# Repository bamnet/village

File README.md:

# Village Electric Light Department

_(village, for short)_

## Background

I have a collection of 1-2 dozen Department 56 lighted Christmas houses. The default
lighting solution has a big problem though: a house is either lit or not. Further,
the default technique of daisy-chaining all of the plugs together means the entire
village is typically on or off.

This is not very realistic, our winter Dickens Village is not North Korea.

## Goal

The Village Electric Light Department provides the ability for each house to be
individually dimmed and to have that brightness vary throughout the night. This
enables much more custom and realistic displays, with each house following its
own lighting pattern throughout the night and across different nights.

## Approach

### 2018?

In 2018 we built our first prototype. To do this, we bought an RGB LED strip and cut
it into individual segments. We soldered wires onto each segment, and wired them all
back into a TLC5947 controlled by an ESP32.

Each house got one cut segment of a 12 V analog (not individually addressable) RGBW
strip (Shiji Lighting SJ-10060-RGBW, 60 LEDs/m). A segment has 3 warm-white 5050 RGBW
LEDs. Each color channel runs its 3 LEDs in series with a current-limiting resistor
(150 ohm on G/B/W), roughly 20 mA per channel. The TLC5947 sank each channel's
current. See `archive/2018_led_segment.jpg`.

This was a good proof of concept, but the construction was quite messy with flexible
LED strip segments haphazardly positioned in the back / bottom lighting holes of the
houses, a messy breadboard wiring this all together, and standalone power supply.

### 2020?

We started cleaning up this design by introducing a circular PCB with LEDs that we
could fit into a 3D printer holder for each house. These could, in theory, be wired
back to a base station for control.

Ultimately, we never finished a working end-to-end design here, largely driven by
the manual work to solder connectors onto each of the PCBs and, more importantly,
the manual work to build custom cables to connect the PCBs back to the base station.

### 2025

We specified a two-board design (ESP32-S3 base station running WLED, plus a
daisy-chained 20 mm Pixel PCB with SK6812 RGBW LEDs) and started a controller
layout. Nothing was fabricated because we ran out of time.

## Specifications

Requirement keywords (MUST, SHOULD, MAY) follow RFC 2119. Items marked **TBD** are
open decisions.

### System

- The system MUST support 22 houses.
- Each house MUST be independently addressable, so its brightness can be set on
  its own. Addressing each LED within a house MAY be supported, but is not required.
- Houses SHOULD be daisy-chained, with the base station driving about 4 chains
  (roughly 6 houses per chain). This keeps cables short and the base station tidy.
  It is a preference, not a hard requirement: another topology is acceptable if
  it is clearly better.

### Physical layout

- Tentatively, the base station sits in the middle, between two shelves, with chains
  running outward on both sides.
- Houses are spaced about 1 ft (0.3 m) apart. A house-to-house cable of about 1 m
  gives enough slack.
- The farthest house is no more than 8 ft (2.4 m) from the base station.

### Light

As a winter village, each house MUST be lit using warm white light. Each house MAY
support RGB to fine tune the colors and do neat patterns.

The light should be bright, historically using a 5 - 6 watt C7 bulb @ 120 volts.
We obviously want to modernize this with an LED.

- Research (2026-09) shows small incandescent C7 bulbs are dim. Retail listings give
  a 4 W clear C7 as 16 - 19 lm, and a 5 W, 130 V-rated C7 as about 10 lm. LED
  "5 W equivalent" C7 bulbs claim 50 - 75 lm, but those figures are marketing, not
  measurements. The 2025 spec's "~60 lm" target is probably 3x too high.
- The 2018 prototype segment was bright enough, even with its poor LED placement on
  a flexible strip. It had 3 warm-white RGBW 5050 LEDs per house, each channel's LEDs
  in series at about 20 mA.
- Brightness target: warm-white output per house SHOULD match the 2018 segment,
  meaning 3 warm-white RGBW 5050 LEDs driven at about 16 - 20 mA.
- Each house MUST use one WS2814 as its driver. It is a 4-channel RGBW
  constant-current driver that WLED supports (configured as SK6812 RGBW type). Its
  outputs are fixed at 16.5 mA per channel, about 80% of the 2018 current.
  **TBD:** confirm this is bright enough.
- As of 2026-09-30, the original SOP-12 WS2814 (C965562) shows 0 stock at LCSC.
  The draft schematic uses the WS2814F (FSOP-8, C5446694, about 107,000 in stock).
  It has the same 16.5 mA outputs, the same 9 V DIN rating, and the same 12 V
  application circuit (2.7k to VDD, 0.1 uF). It has no backup data input (DIN2),
  so there is nothing to tie off. Its data order is W, R, G, B (datasheet p. 4).
  The WS2814A (SOP-8, C2920044, about 7,800 in stock) is the same die in a larger
  package. It is the fallback, with a standard SOIC-8 footprint.
- Decided (2026-09-30): the Pixel PCB uses the WS2814F. Its smaller body leaves
  more room for the LEDs on the 20 mm board.
- The WS2814F's FSOP-8 footprint (1.65 x 3.25 mm body, 2.85 mm lead span, 0.8 mm
  pitch) is not in KiCad's stock libraries, so we drew it. Once it's proven on a fabricated
  board, consider contributing it (and a WS2814 symbol) upstream to the KiCad
  libraries.
- Each channel drives 3 LEDs in series, and all 3 LEDs show the same color, with one
  address per house. The white channel MUST be warm white (2700 - 3000 K).
- LEDs SHOULD be 3 RGBW 5050 4-in-1 packages with a warm-white die, matching 2018.
  Fallback: 3 RGB LEDs plus 3 separate warm-white LEDs, which also allows a free
  choice of warm-white LED.
- As of 2026-09, LCSC has two warm-white 4-in-1 RGBW 5050 parts (SMD5050-8P, with
  a separate anode and cathode pin per color). Both are JLCPCB extended parts.
  Figures are from the datasheets, at 20 mA:
  - Honglitronic HL-5050RGBW-S1-A27 (C22470444): about 11,000 in JLCPCB stock.
    The "-A27" suffix is the datasheet's white bin A27, which is 2580 - 2870 K.
    That is slightly warmer than 2700 - 3000 K at the low end. White gives 7 - 9 lm,
    CRI 80 or better. Forward voltage is 2.8 - 3.4 V (W/G/B) and 1.8 - 2.4 V (R).
  - TCWIN TC5050RGBW3D06-4CSAR3-AFW324A (C784543): 2800 - 3200 K. White gives
    6 - 7 lm, CRI 80 - 85, with a forward voltage of 2.8 - 3.2 V. Stock is low
    (about 240 at JLCPCB, 860 at LCSC).
  - Cool-white variants that do not meet the spec: XINGLIGHT XL-5050RGBW
    (C7371891), TCWIN C784545 (6000 - 6500 K), and C784544 (3800 - 4200 K).
  **Chosen: Honglitronic C22470444.** We tested samples of both parts in 2026-11.
  The Honglitronic white was warmer and slightly preferred. Its spec sheet
  (B-18-A-1651 rev A/2, 2019) has "Under Development" checked on its cover, not
  "Mass production", but JLCPCB stocks it, so this looks like stale paperwork.
- Heat is not expected to be a concern. The cut-up LED strip prototype ran without
  heat problems.
- Driver heat (estimated): 3 red LEDs drop only 5.4 - 7.2 V, which leaves up to
  about 6.6 V across the WS2814's red output (about 110 mW at 16.5 mA). The draft
  adds a 120 ohm ballast resistor (R4) on red to take about 2 V (33 mW) of that off
  the chip. With all four channels at full, the WS2814 then dissipates about
  0.2 W worst case. Warm-white-only use is well below this.
- The two LED candidates number their pins differently. Honglitronic has anodes on
  pins 1/3/5/7 (W/B/G/R) and cathodes on 2/4/6/8. TCWIN has anodes on 1-4 (R/G/B/W)
  and cathodes on 8-5. Physically they match: with the corner mark at the top
  left, looking at the lens, both put the anodes on the right with white at the
  top, and each cathode is directly across from its anode. A multimeter check of
  both samples (2026-11) confirmed this for white. The schematic and footprint use
  the Honglitronic numbering.

### Interconnect

The lack of a practical cable solution is what stalled the 2020 attempt, so it is a
first-class requirement here.

- Cables MUST be off-the-shelf or easily purchasable. We MUST NOT need to crimp,
  solder, or otherwise build our own cables (the system needs about 24 of them).
- House-to-house links need cables of about 1 m. **TBD:** the length from the base
  station to the first house in each chain.
- The WS2814 datasheet specifies data runs of up to 2 m between two points without
  extra circuitry. The base-station-to-first-house run SHOULD stay within about 2 m.
  Otherwise the base station needs a stronger line driver.
- Cables MUST be standard 3-wire RC servo extension cables (JR/Futaba style, 2.54 mm
  pitch), bought ready-made. 1 m male-to-female cables are widely sold. 22 AWG is
  preferred over 26 AWG for lower voltage drop.
- Boards MUST use 2.54 mm pitch 1x3 headers: male pins for the incoming cable and a
  female socket for the outgoing cable. JLCPCB SHOULD solder these through-hole
  parts (v0.1 headers were hand-soldered; see the Pixel PCB section).
- Pinout MUST put power on the middle pin, following the servo convention. Then a
  reversed plug swaps ground and data rather than shorting the supply. The design
  SHOULD tolerate a reversed plug without damage, using series resistors on data
  lines and similar measures. This is to be verified during design: in a reversal,
  a house's ground rides on the upstream data line, and the WS2814 data input is
  rated to only 9 V.
- Draft protection (Pixel PCB schematic v0.1, estimated rather than tested):
  - Reversed plug: this house's GND pin lands on the upstream data line. The
    return current of this house and every house downstream is about 2.6 mA per
    house through its 2.7k VDD resistor, so about 16 mA for 6 houses, since the
    LEDs stay dark with no valid data. Most of it flows through the upstream
    house's R3 (100 ohm) into the upstream WS2814's DOUT. For the first house in
    a chain, it flows into the Dig-Quad's output buffer instead. Only about
    1 - 2 mA goes through this house's R2 (1k) and D1. The part at risk is
    therefore the upstream driver. The datasheet rates DOUT sink current at 10 mA
    minimum at 0.4 V (p. 3), which is less than 16 mA. While the upstream DOUT is
    high, this house's ground rises to about 5 V. The current then splits between
    R2/D1 (about 5 mA) and the upstream chip's VDD. D1's job is to clamp DIN so it
    can't go below this house's lifted GND.
  - Offset plug (a socket shifted one pin over on the header): 12 V can land on the
    data pin. R2 limits this to about 7 mA into VDD through D1, so R2 dissipates
    about 45 mW (the 0402 is rated 62.5 mW). The pass/fail limit is the datasheet's
    VDD absolute maximum of 3.7 - 5.3 V (p. 2), so VDD must stay at or below 5.3 V.
  - Why keep D1: the datasheet limits logic input voltage to "VDD-0.7 ~ VDD+0.7"
    (p. 2). The lower bound is almost certainly a typo for -0.7 V. Either way, DIN
    may go only about 0.7 V beyond the rails. The BAT54S (Vf about 0.3 V) keeps
    DIN inside that window in both the reversed and offset cases. A series
    resistor alone would not.
  - DOUT keeps the datasheet's 100 ohm series resistor.
  - **TBD:** the R2 value. Test on the first fabricated Pixel boards (the LED
    samples on order don't include a WS2814F):
    - Reversed plug: check that the upstream DOUT and the Dig-Quad output survive
      and still work afterward.
    - Offset plug: measure VDD with 12 V on DATA_IN. It must stay at or below 5.3 V.
    No circuit change is planned until those results are in.
- Flat servo cable fits the original cord channel. It is thinner than the classic
  120 V lamp cord that already uses it.

### Power

- The system MUST use a 12 V supply. We chose 12 V over 5 V because of voltage drop.
  5 V SK6812 LEDs need at least 4.5 V at the last house, which leaves only about
  0.5 V for losses across a chain of servo cables. At 12 V, 3 white/blue/green LEDs
  in series need about 9 - 9.6 V (3.0 - 3.2 V each). Allowing for the driver output,
  that leaves roughly 1.5 V of headroom. These are estimates: the WS2814 datasheet
  does not specify the minimum output voltage it needs to regulate.
- Estimated load: about 66 mA per house with all four channels at full, so about 1.5 A
  (18 W) for 22 houses. With warm white only, it is about 16.5 mA per house, so about
  0.4 A.
- Estimated voltage drop: about 0.6 V at full RGBW for a 6-house chain on 26 AWG
  cable (about 2 m to the first house, then 1 m hops). This is within the headroom.
- For the prototype, power enters through the Dig-Quad's input screw terminals.
  **TBD:** a supply sized with margin (for example 12 V, 3 A or more).

### Pixel PCB

- The project targets KiCad 10. Files saved in KiCad 10 cannot be opened in
  KiCad 9.
- Draft schematic: `hardware/pixel/pixel.kicad_sch` (v0.1). It was authored in
  KiCad 9 format and is ERC clean in KiCad 9.0.2 and 10.0.6.
- Custom footprints live in the project library `hardware/pixel/village.pretty`
  (nickname `village`), since neither part is in KiCad's stock libraries:
  - `FSOP-8_1.65x3.25mm_P0.8mm` (U1, WS2814F). From the datasheet package drawing
    (V1.1, p. 6): 0.35 mm leads with 0.4 mm feet. The land pattern is 0.9 x 0.45 mm
    pads centered 2.6 mm apart (0.3 mm toe, 0.2 mm heel).
  - `LED_Honglitronic_HL-5050RGBW_5.0x5.0mm_P1.2mm` (D2-D4). This is the
    manufacturer's recommended land pattern (spec B-18-A-1651 rev A/2, p. 3):
    1.1 x 0.54 mm pads, 2.83 mm inner gap, 1.2 mm pitch. Pads are numbered as in the
    datasheet's top view: anodes 1/3/5/7 on the right, cathodes 2/4/6/8 on the
    left, pin 1 at the top right. The part's corner mark sits at pin 2 (white
    cathode), and the footprint's silkscreen tick and Fab chamfer mark that
    corner. KiCad's usual pin-1 marking would put the tick on the white anode,
    which would make a correctly placed LED look rotated in review.
  - The LED datasheet's "bottom view" labels the pins the same as its top view,
    not mirrored, so one of the two views is wrong. A 2026-11 multimeter check of
    a sample (diode mode, red lead on the anode) showed that the top view is
    correct. With the corner mark at the white cathode, the white anode is directly
    across from it. That is the footprint as drawn, not a mirror image.
  - **TBD:** both footprints are unproven until a fabricated board is assembled and
    works. The TCWIN LED would fit the same pads, but its symbol pin numbers would
    need remapping, because its pad numbering differs.
- In order to fit the 3D-printed holder that sits in each house's lighting hole,
  the per-house PCB ("Pixel PCB") MUST be a circle no bigger than 20 mm in diameter.
  This is small, but large enough to fit several LEDs as needed.
- The lighting hole in the house itself is slightly larger than the holder hole. The
  hole size is broadly consistent across houses (the original lights are
  interchangeable). **TBD:** the measured house hole size.
- Some houses have the lighting hole in the back and some in the bottom. For bottom
  holes, the original clip-in lamp sits in the hole and its cord leaves sideways,
  flush with the base, through a notch and cord channel in the house base.
- For bottom holes, the assembly can extend up to about 1 in (25 mm) into the house.
- A daisy-chained house has two cables (in and out). Both MUST fit through the notch
  and cord channel. Two flat servo cables fit, since a classic 120 V lamp cord does.
- LEDs MUST be on the top side, clustered near the center. Headers (through-hole)
  go on the bottom side.
- All surface-mount parts, the WS2814 included, SHOULD also go on the top side. That
  keeps assembly to one surface-mount side, which is simpler and cheaper. Moving the
  WS2814 to the bottom is allowed if the LEDs don't fit otherwise, but it requires
  JLCPCB two-sided (Standard) assembly. Settled in layout: every surface-mount
  part, the WS2814F included, is on the top side.
- Through-hole header pins and solder joints come out on the LED side. Headers
  MUST sit near the rim, with a centered keep-out for the LEDs.
- Headers SHOULD be right-angle, mounted side by side on the bottom, with both
  pointing the same way (toward the cord notch). The plugs then lie flat under the
  board. This gives a much lower profile than vertical headers, and both cables
  already point where they need to go. JLCPCB-assemblable candidates: male C492411
  and female C2897385. If two plugs don't fit side by side on the 20 mm board, fall
  back to vertical headers. **TBD:** confirm the fit with real servo plugs (the
  width is estimated at about 8 mm each).
- Provisional layout (placed and routed, pending real plug dimensions):
  `hardware/pixel/pixel.kicad_pcb`.
  - The board is a 20 mm circle. The cord notch is taken to be at the south
    (+Y) edge.
  - J1 and J2 are on the bottom side, with pin rows side by side about 4 mm north
    of center. Their bodies point south and run under the board, so the plugs
    mate near the south rim and lie flat. This works because the headers and
    plugs are on the bottom while every other part is on the top, so the header
    bodies can sit under the top-side parts.
  - This relaxes "headers near the rim". The pin rows sit just north of the
    LEDs, and the LED cluster sits about 2.5 mm south of center.
  - The header rows are 8.9 mm apart, center to center. KiCad's stock
    footprints need at least 8.62 mm, which is slightly more than the estimated
    8 mm plug width.
  - J1 and J2 use KiCad's stock right-angle footprints. Checked against the LCSC
    drawings on 2026-09-30, and the copper matches:
    - J1, male (XFCN PZ254R-11-03P, C492411): Ø1.02 mm holes and 0.64 mm square
      pins (0.91 mm across the corners, so they fit the 1.0 mm drill). The
      body's front face is 4.4 mm from the pin row, and the pin tips are at
      10.4 mm (KiCad draws 4.04 mm and 10.04 mm).
    - J2, female (HCTL PM254-1-03-W-8.5, C2897385): Ø1.02 mm holes. The 8.5 mm
      body ends 10.2 mm from the pin row (KiCad draws 10.03 mm), and the body is
      8.02 mm wide (KiCad draws 7.62 mm). A purchased sample measured about
      8.09 mm wide (2026-11).
    - KiCad's courtyards still cover both real bodies. With the rows 8.9 mm apart,
      the bodies are about 1.1 mm apart.
    - The pin tails are 3.0 and 3.2 mm long, so on a 1.6 mm board they stick up
      about 1.4 - 1.6 mm on the LED side.
  - Pin order: the stock footprints put J1's pin 1 at the west end and J2's pin 1
    at the east end, so the two GND pins are adjacent. Neither part is polarized,
    so this only decides which way up each cable plugs in.
  - Silkscreen markings for plugging in and for JLCPCB's assembly review:
    - Bottom: a filled triangle points at each header's pin 1 (data), with "+" and
      "-" at the other pins. These shapes read the same whether or not they are
      mirrored.
    - Bottom: "JLCJLCJLCJLC" marks where JLCPCB should print its order number.
      The 2026-11 order form had no "Specify a location" option, so v0.1 was
      ordered with "Mark on PCB: Remove Mark" instead.
    - Top: "v0.1", and a pin-1 dot inside U1's outline. The footprint's pin-1
      silkscreen line is clipped by J1's GND pad, so without the dot the top and
      bottom lines would look alike.
    - The LEDs keep their pin-1 tick. D1 uses KiCad's stock SOT-23 outline.
  - On the top side, the LEDs follow the chain +12V -> D2 (east, rot 90) -> D3
    (south, rot 0) -> D4 (west, rot 270) -> U1. Each LED faces the side that
    connects to the next LED toward it, so each group of four color nets between
    LEDs fans diagonally with no crossings. D4's R/G/B cathodes sit just below
    U1's matching outputs. U1 is between D4 and D2, with R4 on the red output and
    C1 beside the VDD pin. D1, R1, C2 and R2 sit above the header pin rows.
  - Routed with Freerouting 2.4.1: 4 vias. +12V and GND are 0.4 mm (a Power
    netclass), because up to ~0.4 A passes through to the rest of the chain.
    Signals are 0.2 mm. VDD narrows to 0.15 mm around U1, and the board minimum
    is set to 0.15 mm to allow it.
  - DRC: 0 errors, 0 unconnected. JLCPCB's limits are enforced by
    `pixel.kicad_dru` and the board setup.
  - Routing workflow: export the DSN with KiCad's Python module
    (`pcbnew.ExportSpecctraDSN`). Route with Freerouting's bundled launcher,
    because the standalone jar needs Java 25. Import the session in KiCad with
    File -> Import -> Specctra Session. Konnect's own DSN export refuses this
    board (round outline, back-side headers, custom rules).
  - JLCPCB export: Konnect's `export_manufacturing_package` with the board open in
    KiCad, `fab_house` jlcpcb, all copper/paste/silkscreen/mask layers plus
    Edge.Cuts, BOM fields `Value,Reference,Footprint,LCSC`, and
    `jlcpcb_cpl_corrections_path` set to `jlcpcb_cpl_corrections.json`. That file
    rotates U1 by 270 degrees and D1 by 180 degrees in the CPL. Both values came
    from comparing our footprints with JLCPCB's EasyEDA footprints for the BOM parts.
    The same comparison reproduces Konnect's preview-verified SOIC-8 rule. The LEDs
    need no correction. JLCPCB's placement preview for v0.1 confirmed U1, D1 and
    the LEDs.
  - JLCPCB's Economic assembly is single-sided, so it leaves off the bottom-side
    headers J1 and J2. Standard assembly can do both sides but needs a board of at
    least 70 mm. v0.1 (5 boards) was assembled top side only, with J1/J2
    hand-soldered.
  - **TBD:** for the 22-board run, either order a JLCPCB panel of at least 70 mm
    (for example 4 x 4) with Standard two-sided assembly, or move the headers so
    that single-sided assembly covers them. Hand soldering MUST be kept to a
    minimum.
  - Manufacturing releases live in `hardware/pixel/production/<version>/`, named
    after the silkscreen version. Each has the exact uploaded files and a
    `MANIFEST.md` with the source commit, file hashes, checks, and the order
    record. When an order is placed, fill in the manifest and tag the commit
    `pixel-<version>`. An ordered release is never changed. A design change bumps
    the silkscreen version and gets a new folder.
  - **TBD:** revisit the header positions once real plugs are measured. The
    house holder now favors vertical headers; see "Feedback for Pixel PCB v0.2"
    in the House holder section.
- The connector, the holder, or both SHOULD let the cables make the turn into the
  channel without stressing the connectors or their solder joints.

### House holder

A 3D-printed holder fits each Pixel PCB into a house's lighting hole. The houses are
Department 56. Their stock cord holds the bulb with bent spring-steel clips that
grip the hole's edge.

Draft OpenSCAD: `hardware/holder/` (OpenSCAD 2021.01). Z = 0 is the wall's outer face,
and +Z points into the house.

#### Measurements

- 2026 notes (7 houses): hole Ø25 - 28 mm, wall 3 - 6 mm. Three bottom-lit houses
  also have an "inlet" of 12 - 13 mm, which is the depth of the recess around the
  hole.
- 2021 spreadsheet (12 houses): wall 4 - 8 mm (8 is the Bakery).
- The same houses differ between the two years by up to 2 mm (Fezziwig 4 vs 6,
  Curiosity 5 vs 4). Treat this as measurement noise.
- The 2021 printed plugs (gcode, reconstructed from the toolpaths):
  - a Ø32.6 x 2.7 mm flange with a Ø14.4 mm center hole;
  - a Ø21.9 mm bore for the old 21 mm board;
  - a tube whose rib narrows from Ø28.4 to about Ø24 over 15 mm, for a total
    height of 17.6 mm. The rib appears to be a coarse tapered thread, about 6 mm
    pitch.

  One print fit 11 of 12 houses. Mutton's hole was 1 - 2 mm too small.

#### Requirements

- Holders are temporary. They MUST come out before the houses are packed away and
  survive yearly insertion and removal.
- One size MUST fit all houses. At worst, there may be one bottom-lit and one
  back-lit variant. We cannot measure every Department 56 piece.
- Design range: hole Ø24 - 29 mm, wall 3 - 9 mm.
- Bottom-lit houses have a recess around the hole. None is known without one.
  Everything below the wall MUST fit inside the shallowest recess (12 mm measured)
  and inside its outline.
- The holder may reach up to 25 mm into the house.
- The PCB SHOULD sit inside the house, above the wall's inner surface, so the
  hole's rim doesn't block the light. That calls for vertical headers: the plugs
  then hang straight down through the hole. (The right-angle-header draft, which
  kept the PCB outside the wall, is preserved at git tag
  `holder-right-angle-draft`. Its arms formed a tall tube around the LEDs that
  passed only about 20% of the light directly.)
- The cables MUST be able to leave toward the cord notch (bottom-lit) or
  downward (back-lit).
- A tug on a cable MUST load the holder, not the headers' solder joints. The
  plugs MUST NOT slide off their headers, even hanging plug-down.
- Print in PETG on the Ender 3 Pro (0.4 mm nozzle), without supports where
  possible.

#### Design (draft, vertical headers)

One printed part, `holder.scad`:

- **Clip ring** (`clip.scad`): a flange (Ø34 x 2.4 mm, Ø26.4 opening) sits against
  the outside of the wall. Three arms rise through the hole, each with a barb on
  its free end.
  - The arms curve around the axis and flex in the XY plane, so the layer lines
    never take bending loads.
  - The hole's inner edge rests on the barb's sloped lower face. The arm springs
    outward, and the slope turns that into a pull that holds the flange against
    the wall, for any wall from 3 to 9 mm.
  - The same slope resists pulling out, but a firm pull removes the holder.
  - How hard each arm presses depends on how far it is bent, which is set by
    the hole and the wall: the barb's face radius at the wall's inner edge, minus
    the hole radius.
    - Loosest fit: Ø29 hole, 3 mm wall. Only 0.5 mm of preload in the baseline
      design.
    - Most bend while installed: Ø24 hole, 9 mm wall, about 4.5 mm.
    - Insertion: the barb tip must squeeze through Ø24 whatever the wall.
  - Arms are about 19 mm long. Root strain when squeezed through a 24 mm hole is
    about 1.8 - 2.2%, which suits PETG.
  - The arm tops are 15.7 mm into the house (40 degree lead-in).
- **Posts:** the three arm roots continue up past the arms. Each has a ledge under
  the PCB's edge and a hook lip over it, so the board snaps in from above, LED
  side up.
  - The roots thicken inward (to r 7.5 mm) below the arm tops, to anchor the
    arms.
  - The hooks sit where the board's top-side parts leave room.
- **PCB position:** the board's underside is 17.1 mm into the house and the LED tops
  are at 20.3 mm, above the thickest wall. The ring is turned (`arm_rot`) so the
  barbs, which bend inward furthest, point away from the plugs.
- **Plugs:** both hang straight down the middle and end flush with the flange's
  underside. J1 (male header, 2.5 mm body + 14.5 mm plug) and J2 (5 mm low-profile
  socket + 14.5 mm plug) set the board height.
- **Cables:** a cable tie through one of four slot pairs in the flange straps both
  cables to the flange's underside, pointing toward the cord notch. That holds
  the plugs on, takes tugs off the headers, and gives a handle to pull the holder
  out. A groove on the wall side keeps the tie flush.
- In bottom-lit houses, only the flange (2.4 mm) and the cables' bend sit in the
  recess.
- `pixel_mock.scad` models the board (KiCad courtyards) with vertical headers,
  plugs and cables. `assembly.scad` shows the holder installed in a wall section.
  Its `check` setting renders overlaps:
  - `holder_mock`: the holder at rest against the board, headers, plugs and
    cables. Empty; the hook lips only touch the board.
  - `sweep_mock`: the space the arms sweep through when squeezed through a 24 mm
    hole. It overlaps the east corner of the J2 socket and plug by up to about
    0.4 mm (0.3 mm³; still about 0.1 mm³ at a 25 mm hole). See the open items.

#### Open items

- **TBD:** servo plug dimensions. The model assumes 7.8 x 2.54 x 14.5 mm. The
  plug lengths set the board height.
- **TBD:** a low-profile 1x3 female socket for J2, about 5 mm tall. A standard
  8.5 mm socket raises the board by 3.5 mm, to LED tops at about 23.8 mm (the
  limit is 25).
- **TBD:** the arm sweep reaches the J2 corner in 24 - 25 mm holes. v0.1's pin
  rows are 4 mm north of center, so the plug block's corners sit at r 9.95 - 10.07
  mm, only 0.3 - 0.45 mm inside the arms. Touching only while pushing in is
  harmless. But in a small hole the arm stays bent, and its grip would rest
  partly on the plug instead of the wall. Fix on v0.2 (see the Pixel PCB items
  below) or by narrowing the plugs' spacing.
- **TBD:** the cable bend: two cables turn 90 degrees right under the flange
  (inside the recess, or behind a back-lit house). Check with real cables.
- **TBD:** the LED package height (assumed 1.6 mm).
- The post hooks and ledges are first guesses. Tune them once the clip ring is
  proven. Coupon variant C's arms (top 16.9 mm) are too tall for the current
  board height; it is in the coupon only to test the barb slope.

#### Feedback for Pixel PCB v0.2

- Keep the vertical headers on the bottom, with a low-profile female socket for
  J2.
- Keep the plug block clear of the arms' sweep: every header and plug corner
  within about r 9.5 mm. For example, move the pin rows about 1 mm toward
  center.
- Keep a clear ring at the edge of the top side for the hook lips (parts at
  r ≤ 9.25 mm). The south LED (D3) reaches r 9.62 mm.
- Add an orientation feature, such as a notch, flat or small hole at the edge,
  so the board seats the same way every time.
- White solder mask, as the 2025 spec asked; v0.1 is green.
- Center the LED cluster (v0.1's sits about 2.5 mm south of center).

#### Test plan

1. Print `coupon.scad`: four clip ring variants, with the letter engraved on the
   flange.
   - A: 1.0 mm arms, barb slope 0.25, 0.5 mm preload in the loosest hole (the
     baseline).
   - B: 1.2 mm arms (stiffer).
   - C: 1.0 mm arms, slope 0.4 (more pull-in at thick walls).
   - D: 1.0 mm arms, 1.0 mm preload in the loosest hole.
2. Print `test_rings.scad`: four wall stand-ins at Ø24/Ø29 x 3/9 mm. Measure each
   printed bore with calipers.

   Ready-to-print STLs for steps 1 and 2, with print settings, are in
   `hardware/holder/production/coupon-v0.1/`. Record results in its
   `MANIFEST.md`. As with the PCB releases, a printed package is never changed;
   a design change gets a new folder.
3. For each variant, in each ring:
   - it pushes in by hand;
   - the flange sits tight against the ring;
   - it pulls out without damage.
4. Check the hardest cases:
   - Grip: hang the Ø29 x 3 ring (the loosest fit) from the clip ring with a
     cable's weight, and check that it stays put.
   - Creep: leave each variant in the Ø24 x 9 ring (the most bend) for a day or
     more. Check that it still grips the Ø29 x 3 ring afterward.
   - Wear: insert and remove about 20 times in any ring, and check that the
     arms still spring back.
5. When the boards and cables arrive: solder vertical headers to one v0.1
   board, measure the plugs, and update `params.scad`. Then print `holder.scad`
   with the best variant's arms. Check the snap-in, the cable tie, the cable bend
   in a real recess, and the light inside a house.

### Base station

- For prototyping, we will buy an off-the-shelf WLED controller instead of designing
  one, so the effort goes into the Pixel PCB. A custom base station is deferred. The
  requirements below still apply to whatever we use. The prototype controller is the
  QuinLED Dig-Quad (pre-assembled): 4 level-shifted outputs, 12 V capable, and a
  plug-in fuse per pair of outputs, which should be sized to protect the servo cables.
- For the prototype, each chain connects to the Dig-Quad's screw terminals using a
  servo extension cable cut in half, with the ends stripped. This is an accepted
  exception to the no-built-cables rule, since it needs no soldering or crimping.
- The base station does not have any sizing constraints.
- It MUST be compatible with [WLED](https://kno.wled.ge/) (ESP32-based), so we can get
  started quickly. Custom firmware is a future goal and is out of scope for now.
- Because of that, the LED or driver IC on the Pixel PCB MUST be one of the LED
  types WLED supports.
- The WS2814 data input needs a logic-high of at least 0.7 x VDD (about 3.5 V), which
  is above the ESP32's 3.3 V. Each chain output MUST go through a 5 V level shifter
  (for example 74AHCT125) and a series resistor.
- It MUST have enough chain outputs for the chosen topology (about 4).
- No extra features, such as sensors or current monitoring, are required.

### Manufacturing

- Both boards SHOULD be assembled by JLCPCB, as completely as possible, including the
  connectors. Hand soldering MUST be kept to a minimum.
- Minimize cost per house, but pay for factory assembly rather than hand work where
  there is a trade-off.

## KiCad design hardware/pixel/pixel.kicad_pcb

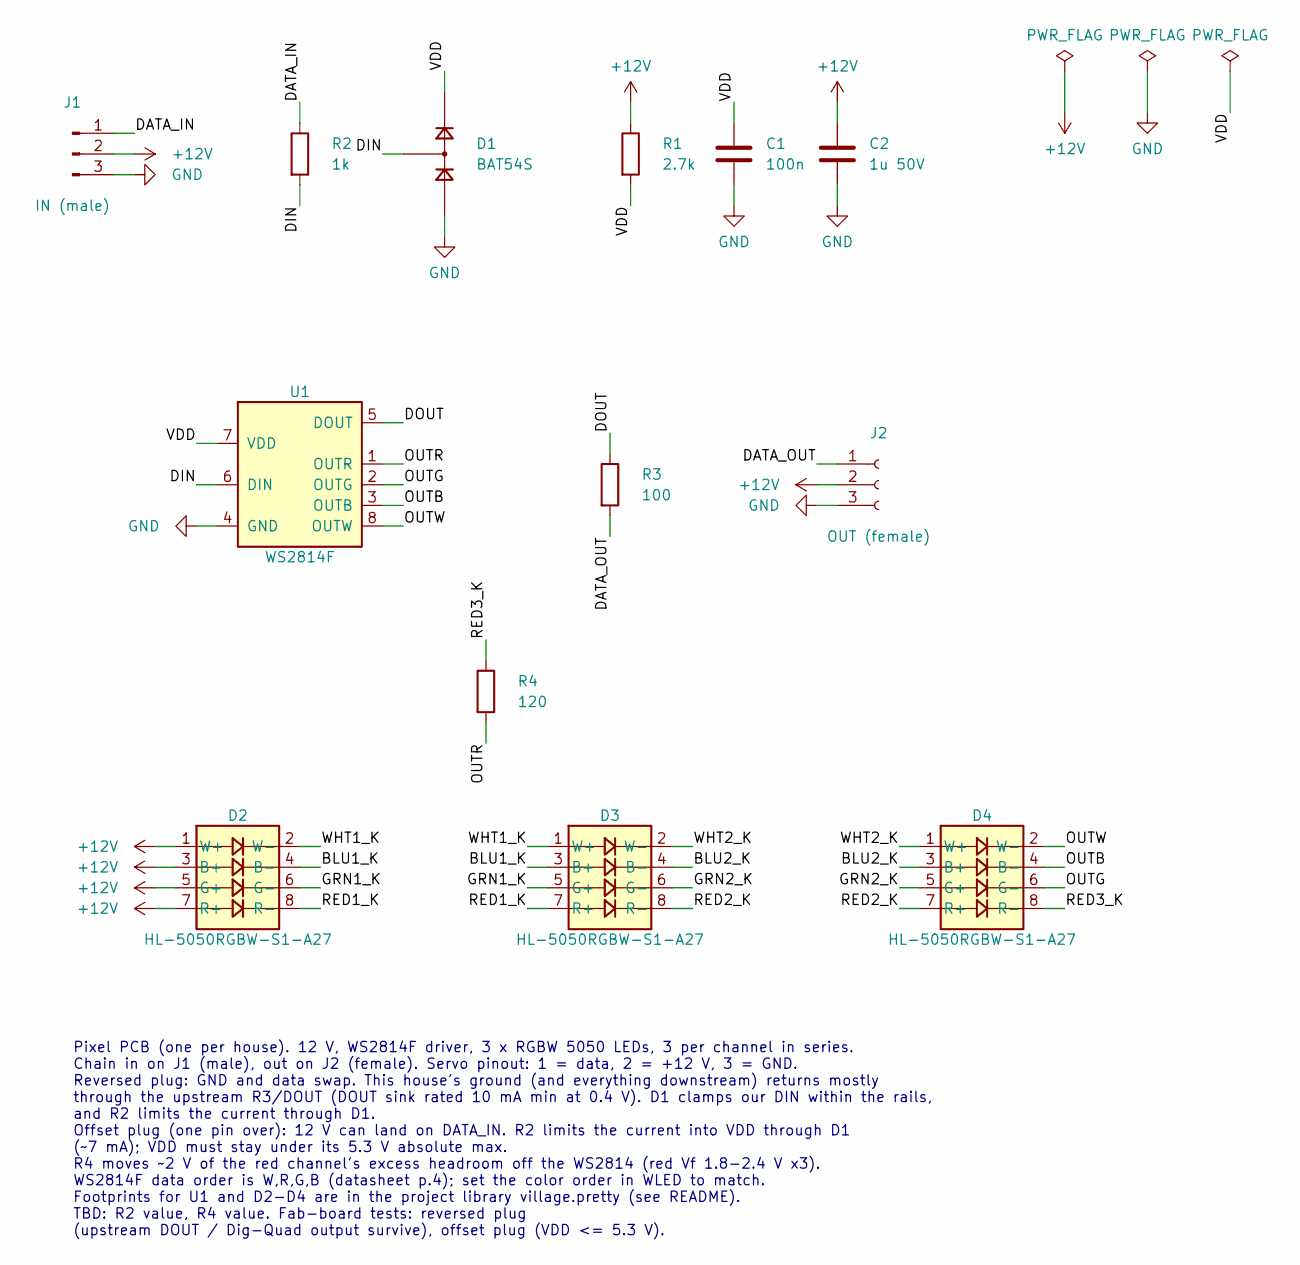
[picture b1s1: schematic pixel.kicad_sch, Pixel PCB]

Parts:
C1: 100n; C_0402_1005Metric; MPN CL05B104KO5NNNC; LCSC C1525
C2: 1u 50V; C_0603_1608Metric; MPN CL10A105KB8NNNC; LCSC C15849
D1: BAT54S; SOT-23; MPN BAT54SLT1G; LCSC C19726
D2, D3, D4: HL-5050RGBW-S1-A27; LED_Honglitronic_HL-5050RGBW_5.0x5.0mm_P1.2mm; MPN HL-5050RGBW-S1-A27; LCSC C22470444
J1: IN (male); PinHeader_1x03_P2.54mm_Horizontal; MPN PZ254R-11-03P; LCSC C492411
J2: OUT (female); PinSocket_1x03_P2.54mm_Horizontal; MPN PM254-1-03-W-8.5; LCSC C2897385
R1: 2.7k; R_0603_1608Metric; MPN 0603WAF2701T5E; LCSC C13167
R2: 1k; R_0402_1005Metric; MPN 0402WGF1001TCE; LCSC C11702
R3: 100; R_0402_1005Metric; MPN 0402WGF1000TCE; LCSC C25076
R4: 120; R_0402_1005Metric; MPN 0402WGF1200TCE; LCSC C25079
U1: WS2814F; FSOP-8_1.65x3.25mm_P0.8mm; MPN WS2814F; LCSC C5446694

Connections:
+12V: C2.1, D2.1 (W+), D2.3 (B+), D2.5 (G+), D2.7 (R+), J1.2, J2.2, R1.1
/BLU1_K: D2.4 (B-), D3.3 (B+)
/BLU2_K: D3.4 (B-), D4.3 (B+)
/DATA_IN: J1.1, R2.1
/DATA_OUT: J2.1, R3.2
/DIN: D1.3 (COM), R2.2, U1.6 (DIN)
/DOUT: R3.1, U1.5 (DOUT)
/GRN1_K: D2.6 (G-), D3.5 (G+)
/GRN2_K: D3.6 (G-), D4.5 (G+)
/OUTB: D4.4 (B-), U1.3 (OUTB)
/OUTG: D4.6 (G-), U1.2 (OUTG)
/OUTR: R4.2, U1.1 (OUTR)
/OUTW: D4.2 (W-), U1.8 (OUTW)
/RED1_K: D2.8 (R-), D3.7 (R+)
/RED2_K: D3.8 (R-), D4.7 (R+)
/RED3_K: D4.8 (R-), R4.1
/VDD: C1.1, D1.2 (K), R1.2, U1.7 (VDD)
/WHT1_K: D2.2 (W-), D3.1 (W+)
/WHT2_K: D3.2 (W-), D4.1 (W+)
GND: C1.2, C2.2, D1.1 (A), J1.3, J2.3, U1.4 (GND)

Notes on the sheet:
Pixel PCB (one per house). 12 V, WS2814F driver, 3 x RGBW 5050 LEDs, 3 per channel in series. Chain in on J1 (male), out on J2 (female). Servo pinout: 1 = data, 2 = +12 V, 3 = GND. Reversed plug: GND and data swap. This house's ground (and everything downstream) returns mostly through the upstream 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

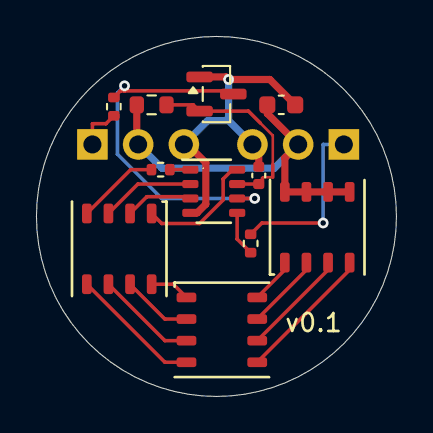
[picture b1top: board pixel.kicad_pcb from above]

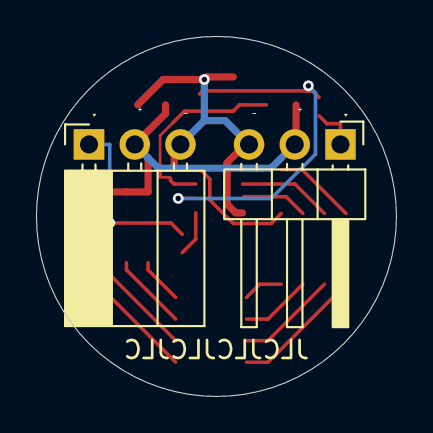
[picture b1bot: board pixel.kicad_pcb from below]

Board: 2 copper layers, 20.0 x 20.0 mm, 13 parts (2 on the bottom side), 20 nets.

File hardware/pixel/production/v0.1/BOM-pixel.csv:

"Comment","Designator","Footprint","LCSC Part #"
"100n","C1","Capacitor_SMD:C_0402_1005Metric","C1525"
"1u 50V","C2","Capacitor_SMD:C_0603_1608Metric","C15849"
"BAT54S","D1","Package_TO_SOT_SMD:SOT-23","C19726"
"HL-5050RGBW-S1-A27","D2,D3,D4","village:LED_Honglitronic_HL-5050RGBW_5.0x5.0mm_P1.2mm","C22470444"
"IN (male)","J1","Connector_PinHeader_2.54mm:PinHeader_1x03_P2.54mm_Horizontal","C492411"
"OUT (female)","J2","Connector_PinSocket_2.54mm:PinSocket_1x03_P2.54mm_Horizontal","C2897385"
"2.7k","R1","Resistor_SMD:R_0603_1608Metric","C13167"
"1k","R2","Resistor_SMD:R_0402_1005Metric","C11702"
"100","R3","Resistor_SMD:R_0402_1005Metric","C25076"
"120","R4","Resistor_SMD:R_0402_1005Metric","C25079"
"WS2814F","U1","village:FSOP-8_1.65x3.25mm_P0.8mm","C5446694"

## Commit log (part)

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2018-12-22 Randomly adjust the brightness of lights.
2018-12-22 Proof of concept scheduler.
2018-12-22 Generate random schedules for each light in the show.
2018-12-22 Build a basic docker image.
2019-01-07 Build arm and amd64 images.
2019-01-08 Add a no-op event so the show doesn't restart until it's done.
2019-12-12 Early draft of new application
2019-12-13 Clean up debug code.
2019-12-13 Add helper functions to control stuff.
2019-12-19 Update main to run the same script as last year.
2020-12-14 Add the bakery
2020-12-14 Notes on how to regenerate protoc
2020-12-14 Update libraries.
2020-12-16 Hardcode the wiring for now.
2020-12-16 Placeholder config setting code.
    The client doesn't like it.
2020-12-16 Try Cloudbuild again.
2020-12-16 Update go build syntax.
2020-12-16 Switch to Go-team's builder.
2020-12-16 Add the dockerfile.
    I knew I was missing something....
2020-12-16 Point builder at input file.
2020-12-16 Error our when connection setup fails.
2020-12-16 Bundle in SSL certs too.
2020-12-16 Initial k8s configs.
2020-12-16 Fix typo.
2020-12-16 The village can run on arm.
2020-12-19 Decrease brightness a tad.
2022-12-19 An app that builds.
2022-12-19 Update C++ standard
2022-12-19 update usb port
2022-12-19 Remove local sdkconfig
2022-12-19 Add flashtype.
